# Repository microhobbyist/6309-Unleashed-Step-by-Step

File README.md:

# 6309-Unleashed-Step-by-Step
 Step by step, per episode, for the 6309 LogicSpark build

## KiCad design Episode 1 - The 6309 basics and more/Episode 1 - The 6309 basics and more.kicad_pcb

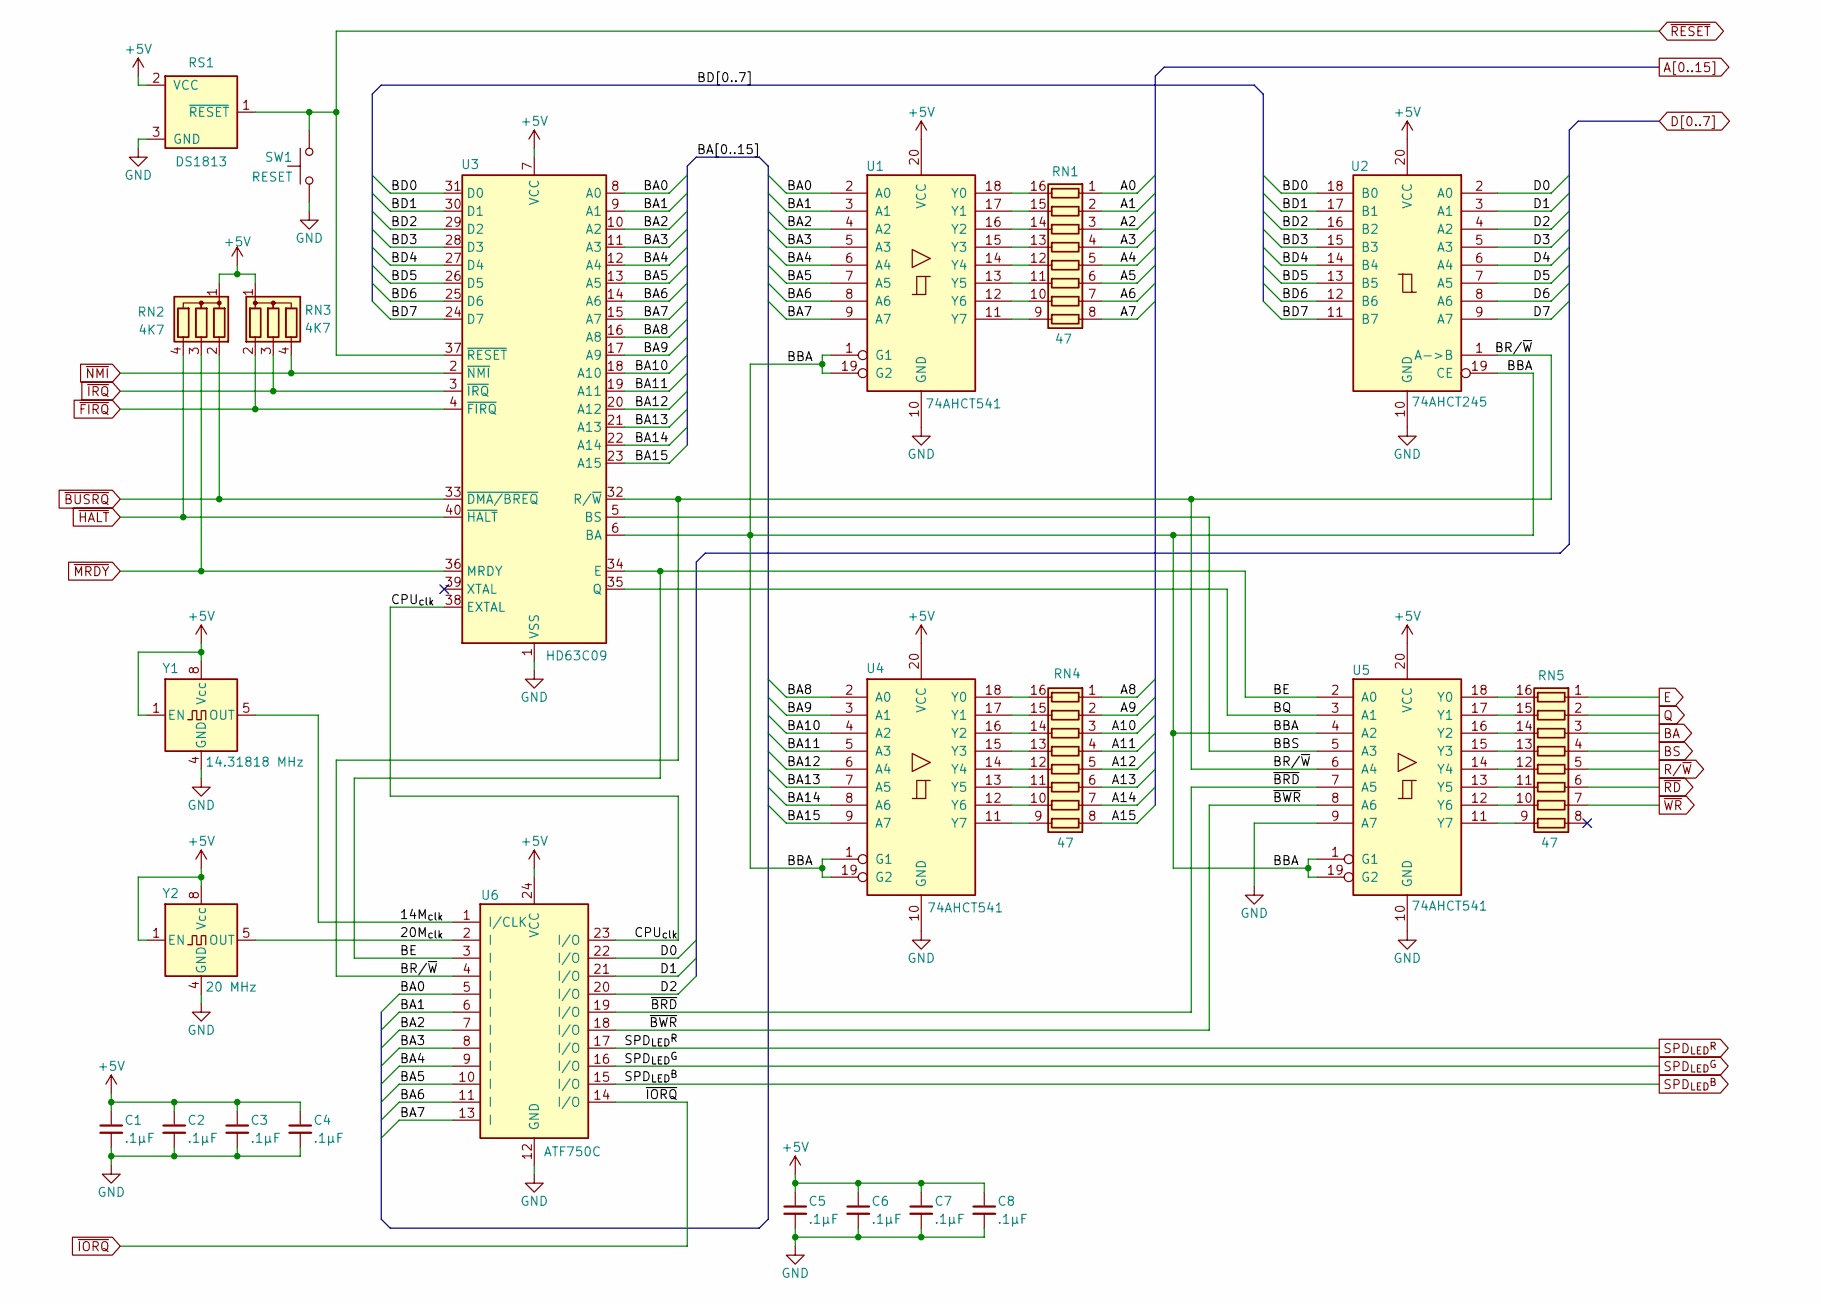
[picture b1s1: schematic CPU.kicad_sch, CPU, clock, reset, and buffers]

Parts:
C1, C2, C3, C4, C5, C6, C7, C8: .1µF; C_Disc_D3.0mm_W1.6mm_P2.50mm
RN1, RN4, RN5: 47; DIP-16_W7.62mm_Socket
RN2, RN3: 4K7; R_Array_SIP4
RS1: DS1813; TO-92_HandSolder
SW1: RESET; SW_Tactile_SPST_Angled_PTS645Vx39-2LFS
U1, U4, U5: 74AHCT541; DIP-20_W7.62mm_Socket
U2: 74AHCT245; DIP-20_W7.62mm_Socket
U3: HD63C09; DIP-40_W15.24mm_Socket
U6: ATF750C; DIP-24_W7.62mm_Socket
Y1: 14.31818 MHz; Oscillator_DIP-8
Y2: 20 MHz; Oscillator_DIP-8

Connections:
+5V: C1.1, C2.1, C3.1, C4.1, C5.1, C6.1, C7.1, C8.1, RN2.1 (common), RN3.1 (common), RS1.2 (VCC), U1.20 (VCC), U2.20 (VCC), U3.7 (VCC), U4.20 (VCC), U5.20 (VCC), U6.24 (VCC), Y1.1 (EN), Y1.8 (Vcc), Y2.1 (EN), Y2.8 (Vcc); also elsewhere on the board
/CPU section/14M_{clk}: U6.1 (I/CLK), Y1.5 (OUT)
/CPU section/20M_{clk}: U6.2 (I), Y2.5 (OUT)
/CPU section/BA0: U1.2 (A0), U3.8 (A0), U6.5 (I)
/CPU section/BA1: U1.3 (A1), U3.9 (A1), U6.6 (I)
/CPU section/BA2: U1.4 (A2), U3.10 (A2), U6.7 (I)
/CPU section/BA3: U1.5 (A3), U3.11 (A3), U6.8 (I)
/CPU section/BA4: U1.6 (A4), U3.12 (A4), U6.9 (I)
/CPU section/BA5: U1.7 (A5), U3.13 (A5), U6.10 (I)
/CPU section/BA6: U1.8 (A6), U3.14 (A6), U6.11 (I)
/CPU section/BA7: U1.9 (A7), U3.15 (A7), U6.13 (I)
/CPU section/BA8: U3.16 (A8), U4.2 (A0)
/CPU section/BA9: U3.17 (A9), U4.3 (A1)
/CPU section/BA10: U3.18 (A10), U4.4 (A2)
/CPU section/BA11: U3.19 (A11), U4.5 (A3)
/CPU section/BA12: U3.20 (A12), U4.6 (A4)
/CPU section/BA13: U3.21 (A13), U4.7 (A5)
/CPU section/BA14: U3.22 (A14), U4.8 (A6)
/CPU section/BA15: U3.23 (A15), U4.9 (A7)
/CPU section/BBA: U1.1 (G1), U1.19 (G2), U2.19 (CE), U3.6 (BA), U4.1 (G1), U4.19 (G2), U5.1 (G1), U5.4 (A2), U5.19 (G2)
/CPU section/BBS: U3.5 (BS), U5.5 (A3)
/CPU section/BD0: U2.18 (B0), U3.31 (D0)
/CPU section/BD1: U2.17 (B1), U3.30 (D1)
/CPU section/BD2: U2.16 (B2), U3.29 (D2)
/CPU section/BD3: U2.15 (B3), U3.28 (D3)
/CPU section/BD4: U2.14 (B4), U3.27 (D4)
/CPU section/BD5: U2.13 (B5), U3.26 (D5)
/CPU section/BD6: U2.12 (B6), U3.25 (D6)
/CPU section/BD7: U2.11 (B7), U3.24 (D7)
/CPU section/BE: U3.34 (E), U5.2 (A0), U6.3 (I)
/CPU section/BQ: U3.35 (Q), U5.3 (A1)
/CPU section/BR/~W: U2.1 (A->B), U3.32 (R/~W), U5.6 (A4), U6.4 (I)
/CPU section/CPU_{clk}: U3.38 (EXTAL), U6.23 (I/O)
/CPU section/~BRD: U5.7 (A5), U6.19 (I/O)
/CPU section/~BWR: U5.8 (A6), U6.18 (I/O)
A0: RN1.1 (R1.1); also elsewhere on the board
A1: RN1.2 (R2.1); also elsewhere on the board
A2: RN1.3 (R3.1); also elsewhere on the board
A3: RN1.4 (R4.1); also elsewhere on the board
A4: RN1.5 (R5.1); also elsewhere on the board
A5: RN1.6 (R6.1); also elsewhere on the board
A6: RN1.7 (R7.1); also elsewhere on the board
A7: RN1.8 (R8.1); also elsewhere on the board
A8: RN4.1 (R1.1); also elsewhere on the board
A9: RN4.2 (R2.1); also elsewhere on the board
A10: RN4.3 (R3.1); also elsewhere on the board
A11: RN4.4 (R4.1); also elsewhere on the board
A12: RN4.5 (R5.1); also elsewhere on the board
A13: RN4.6 (R6.1); also elsewhere on the board
A14: RN4.7 (R7.1); also elsewhere on the board
A15: RN4.8 (R8.1); also elsewhere on the board
BA: RN5.3 (R3.1); also elsewhere on the board
BS: RN5.4 (R4.1); also elsewhere on the board
D0: U2.2 (A0), U6.22 (I/O); also elsewhere on the board
D1: U2.3 (A1), U6.21 (I/O); also elsewhere on the board
D2: U2.4 (A2), U6.20 (I/O); also elsewhere on the board
D3: U2.5 (A3); also elsewhere on the board
D4: U2.6 (A4); also elsewhere on the board
D5: U2.7 (A5); also elsewhere on the board
D6: U2.8 (A6); also elsewhere on the board
D7: U2.9 (A7); also elsewhere on the board
E: RN5.1 (R1.1); also elsewhere on the board
GND: C1.2, C2.2, C3.2, C4.2, C5.2, C6.2, C7.2, C8.2, RS1.3 (GND), SW1.2, U1.10 (GND), U2.10 (GND), U3.1 (VSS), U4.10 (GND), U5.9 (A7), U5.10 (GND), U6.12 (GND), Y1.4 (GND), Y2.4 (GND); also elsewhere on the board
unnamed: RN1.16 (R1.2), U1.18 (Y0)
unnamed: RN1.15 (R2.2), U1.17 (Y1)
unnamed: RN1.14 (R3.2), U1.16 (Y2)
unnamed: RN1.13 (R4.2), U1.15 (Y3)
unnamed: RN1.12 (R5.2), U1.14 (Y4)
unnamed: RN1.11 (R6.2), U1.13 (Y5)
unnamed: RN1.10 (R7.2), U1.12 (Y6)
unnamed: RN1.9 (R8.2), U1.11 (Y7)
unnamed: RN4.16 (R1.2), U4.18 (Y0)
unnamed: RN4.15 (R2.2), U4.17 (Y1)
unnamed: RN4.14 (R3.2), U4.16 (Y2)
unnamed: RN4.13 (R4.2), U4.15 (Y3)
unnamed: RN4.12 (R5.2), U4.14 (Y4)
unnamed: RN4.11 (R6.2), U4.13 (Y5)
unnamed: RN4.10 (R7.2), U4.12 (Y6)
unnamed: RN4.9 (R8.2), U4.11 (Y7)
unnamed: RN5.16 (R1.2), U5.18 (Y0)
unnamed: RN5.15 (R2.2), U5.17 (Y1)
unnamed: RN5.14 (R3.2), U5.16 (Y2)
unnamed: RN5.13 (R4.2), U5.15 (Y3)
unnamed: RN5.12 (R5.2), U5.14 (Y4)
unnamed: RN5.11 (R6.2), U5.13 (Y5)
unnamed: RN5.10 (R7.2), U5.12 (Y6)
unnamed: RN5.9 (R8.2), U5.11 (Y7)
Q: RN5.2 (R2.1); also elsewhere on the board
R/~W: RN5.5 (R5.1); also elsewhere on the board
SPD_{LED}^{B}: U6.15 (I/O); also elsewhere on the board
SPD_{LED}^{G}: U6.16 (I/O); also elsewhere on the board
SPD_{LED}^{R}: U6.17 (I/O); also elsewhere on the board
~BUSRQ: RN2.2 (R1), U3.33 (~DMA/BREQ); also elsewhere on the board
~FIRQ: RN3.2 (R1), U3.4 (~FIRQ); also elsewhere on the board
~HALT: RN2.4 (R3), U3.40 (~HALT); also elsewhere on the board
~IORQ: U6.14 (I/O); also elsewhere on the board
~IRQ: RN3.3 (R2), U3.3 (~IRQ); also elsewhere on the board
~MRDY: RN2.3 (R2), U3.36 (MRDY); also elsewhere on the board
~NMI: RN3.4 (R3), U3.2 (~NMI); also elsewhere on the board
~RD: RN5.6 (R6.1); also elsewhere on the board
~RESET: RS1.1 (~RESET), SW1.1, U3.37 (~RESET); also elsewhere on the board
~WR: RN5.7 (R7.1); also elsewhere on the board

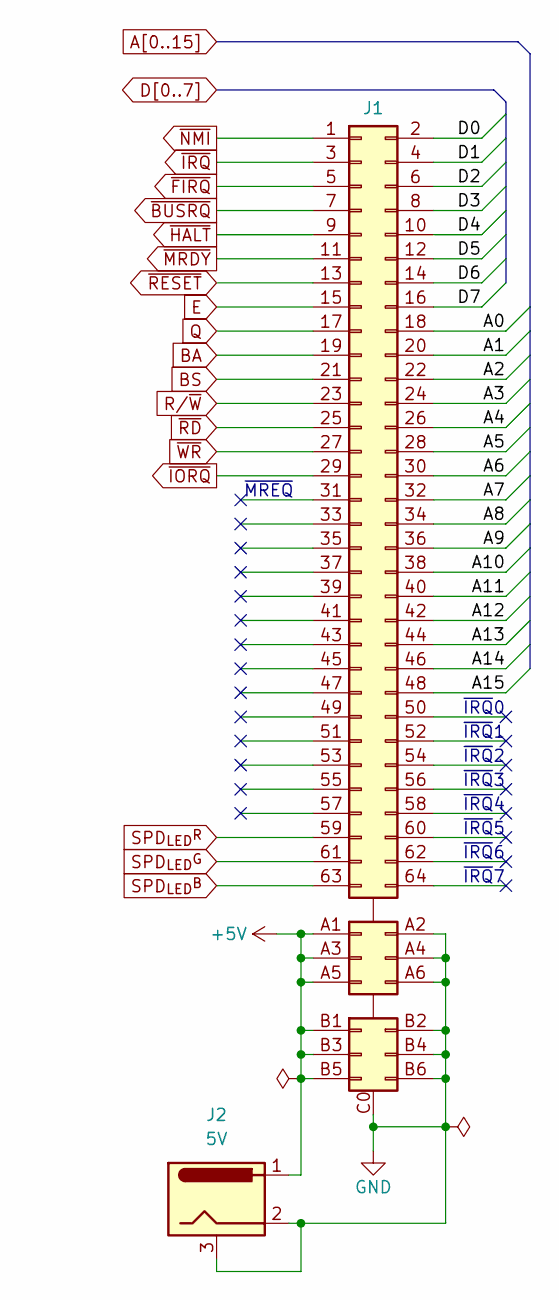
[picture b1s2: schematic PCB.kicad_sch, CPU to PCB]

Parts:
J1: 100mm_Dev_Board; 100x100 dev board with a 64-pin header.
J2: 5V; BarrelJack_Horizontal

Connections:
+5V: J1.A1, J1.A3, J1.A5, J1.B1, J1.B3, J1.B5, J2.1; also elsewhere on the board
A0: J1.18; also elsewhere on the board
A1: J1.20; also elsewhere on the board
A2: J1.22; also elsewhere on the board
A3: J1.24; also elsewhere on the board
A4: J1.26; also elsewhere on the board
A5: J1.28; also elsewhere on the board
A6: J1.30; also elsewhere on the board
A7: J1.32; also elsewhere on the board
A8: J1.34; also elsewhere on the board
A9: J1.36; also elsewhere on the board
A10: J1.38; also elsewhere on the board
A11: J1.40; also elsewhere on the board
A12: J1.42; also elsewhere on the board
A13: J1.44; also elsewhere on the board
A14: J1.46; also elsewhere on the board
A15: J1.48; also elsewhere on the board
BA: J1.19; also elsewhere on the board
BS: J1.21; also elsewhere on the board
D0: J1.2; also elsewhere on the board
D1: J1.4; also elsewhere on the board
D2: J1.6; also elsewhere on the board
D3: J1.8; also elsewhere on the board
D4: J1.10; also elsewhere on the board
D5: J1.12; also elsewhere on the board
D6: J1.14; also elsewhere on the board
D7: J1.16; also elsewhere on the board
E: J1.15; also elsewhere on the board
GND: J1.A2, J1.A4, J1.A6, J1.B2, J1.B4, J1.B6, J1.C0, J1.C1, J1.C2, J1.C3, J2.2, J2.3; also elsewhere on the board
Q: J1.17; also elsewhere on the board
R/~W: J1.23; also elsewhere on the board
SPD_{LED}^{B}: J1.63; also elsewhere on the board
SPD_{LED}^{G}: J1.61; also elsewhere on the board
SPD_{LED}^{R}: J1.59; also elsewhere on the board
~BUSRQ: J1.7; also elsewhere on the board
~FIRQ: J1.5; also elsewhere on the board
~HALT: J1.9; also elsewhere on the board
~IORQ: J1.29; also elsewhere on the board
~IRQ: J1.3; also elsewhere on the board
~MRDY: J1.11; also elsewhere on the board
~NMI: J1.1; also elsewhere on the board
~RD: J1.25; also elsewhere on the board
~RESET: J1.13; also elsewhere on the board
~WR: J1.27; also elsewhere on the board

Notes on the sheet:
~{MREQ}
~{IRQ}1
~{IRQ}0
~{IRQ}5
~{IRQ}6
~{IRQ}2
~{IRQ}3
~{IRQ}7
~{IRQ}4

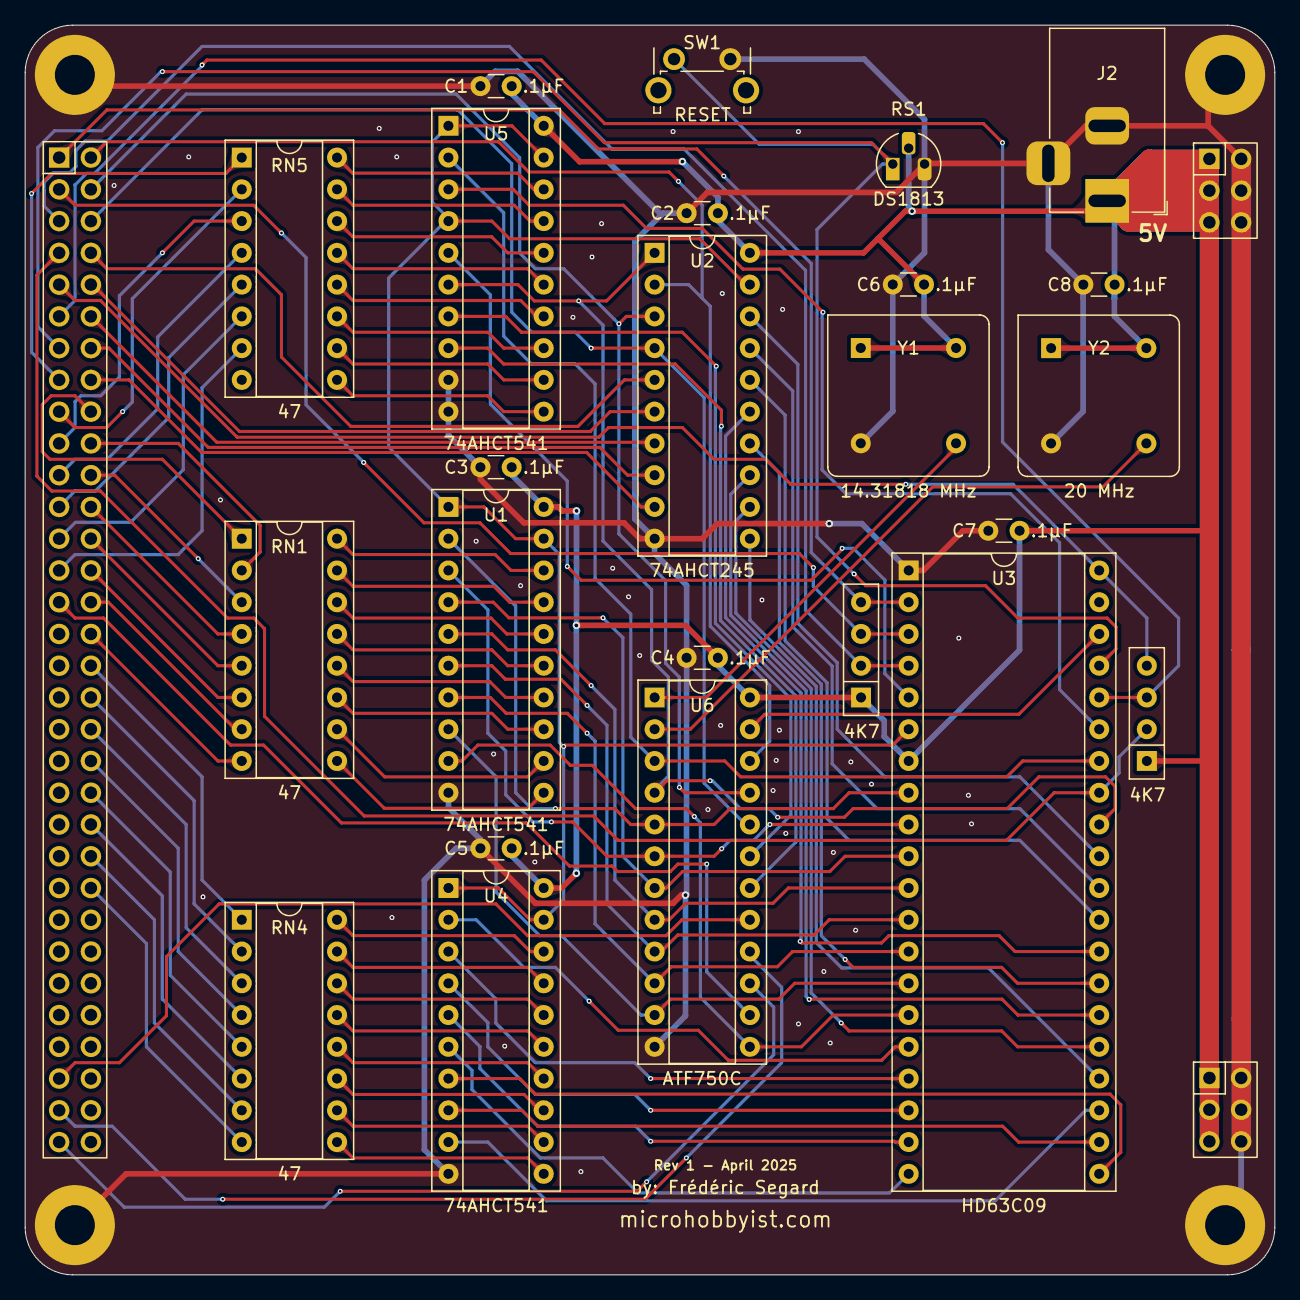
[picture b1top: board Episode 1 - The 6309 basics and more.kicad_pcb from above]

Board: 2 copper layers, 99.9 x 99.9 mm, 25 parts (0 on the bottom side), 102 nets.

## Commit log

2025-03-10 Updating PCB option
2025-03-11 Created the actual PCB
2025-03-13 Dropped the curved traces
2025-04-08 PLD coding
2025-04-09 more PLD stuff
